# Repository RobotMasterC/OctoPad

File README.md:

## OctoPad

*Time is only for PCB*

An 8 key macro pad with 2 knobs that uses KMK firmware

*Image drawn by Ever*

*https://www.youtube.com/@Ever_Draws*

## BOM
- 8x DSA keycaps
- 8x Cherry MX Switches
- 8x SOM123 Diodes (or Any other 1N4148 Diode)
- 4x M3x16 Bolt
- 4x M3 Heatset
- 2x EC11 Rotary Encoder
- 1x XIAO RP2040

## Overall Image

## Schematic

## PCB

## Case

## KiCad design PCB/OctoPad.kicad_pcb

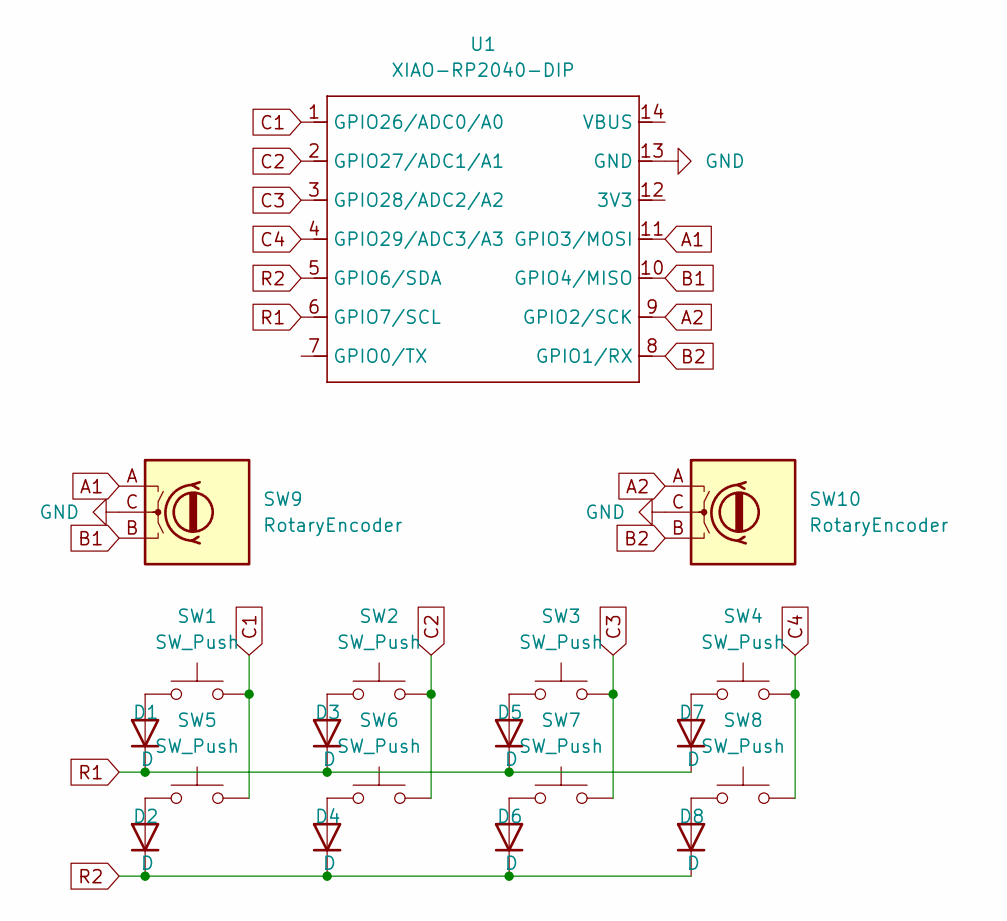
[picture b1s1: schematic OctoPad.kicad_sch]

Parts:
D1, D2, D3, D4, D5, D6, D7, D8: D; D_SOD123_axial
SW1, SW2, SW3, SW4, SW5, SW6, SW7, SW8: SW_Push; SW_Cherry_MX_1.00u_PCB
SW9, SW10: RotaryEncoder; RotaryEncoder_Alps_EC11E_Vertical_H20mm
U1: XIAO-RP2040-DIP

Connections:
A1: SW9.A, U1.11 (GPIO3/MOSI)
A2: SW10.A, U1.9 (GPIO2/SCK)
B1: SW9.B, U1.10 (GPIO4/MISO)
B2: SW10.B, U1.8 (GPIO1/RX)
C1: SW1.2, SW5.2, U1.1 (GPIO26/ADC0/A0)
C2: SW2.2, SW6.2, U1.2 (GPIO27/ADC1/A1)
C3: SW3.2, SW7.2, U1.3 (GPIO28/ADC2/A2)
C4: SW4.2, SW8.2, U1.4 (GPIO29/ADC3/A3)
GND: SW9.C, SW10.C, U1.13 (GND)
unnamed: D1.2 (A), SW1.1
unnamed: D2.2 (A), SW5.1
unnamed: D3.2 (A), SW2.1
unnamed: D4.2 (A), SW6.1
unnamed: D5.2 (A), SW3.1
unnamed: D6.2 (A), SW7.1
unnamed: D7.2 (A), SW4.1
unnamed: D8.2 (A), SW8.1
R1: D1.1 (K), D3.1 (K), D5.1 (K), D7.1 (K), U1.6 (GPIO7/SCL)
R2: D2.1 (K), D4.1 (K), D6.1 (K), D8.1 (K), U1.5 (GPIO6/SDA)

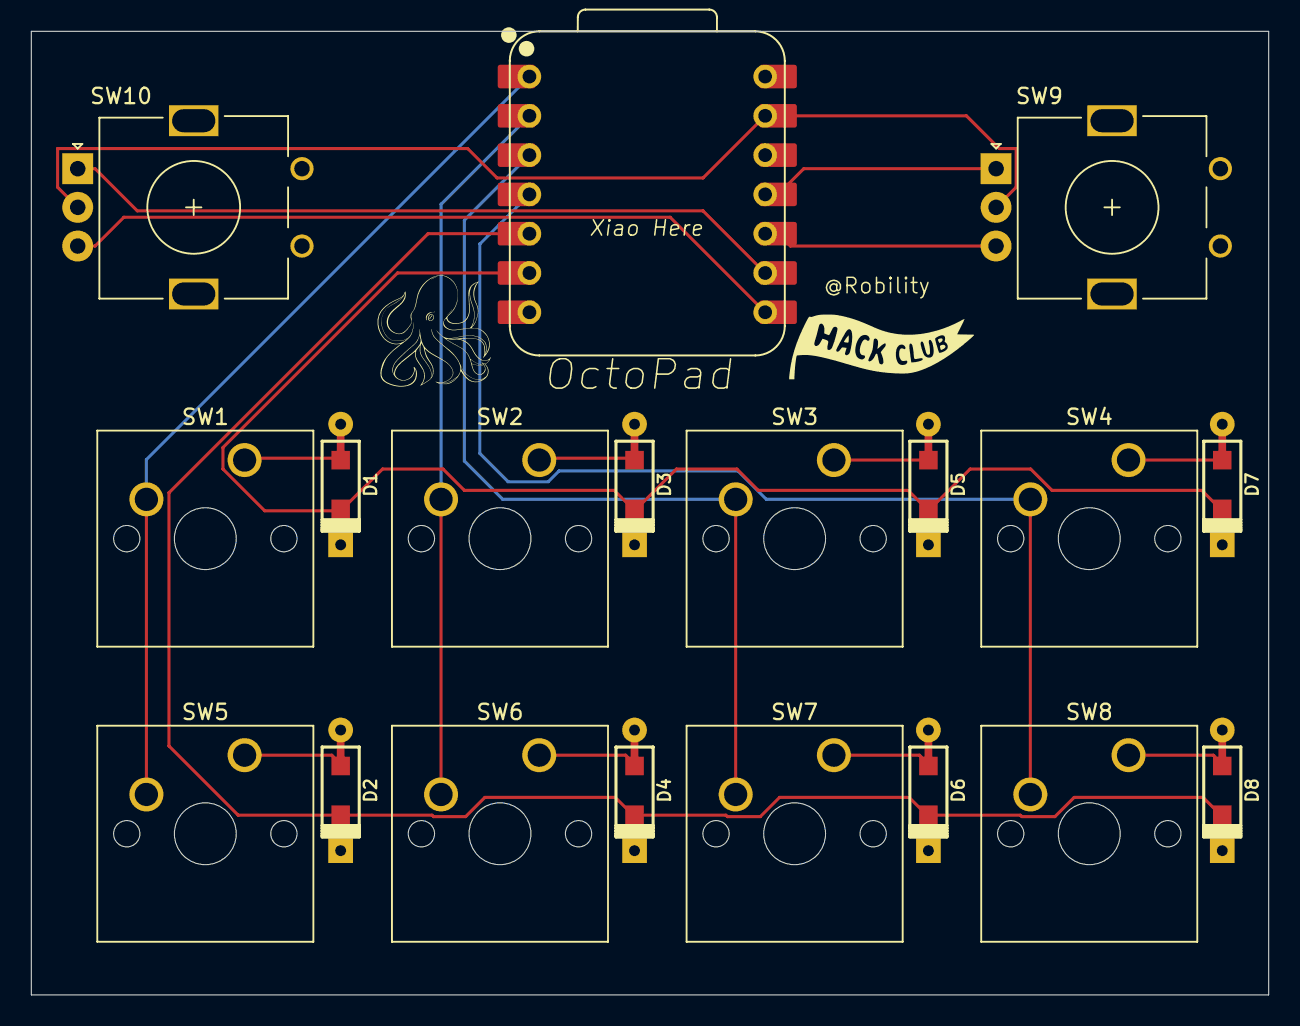
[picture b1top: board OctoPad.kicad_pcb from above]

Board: 2 copper layers, 80.0 x 62.3 mm, 19 parts (0 on the bottom side), 19 nets.

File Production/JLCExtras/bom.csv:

Designator,Footprint,Quantity,Value,LCSC Part #
"D1, D2, D3, D4, D5, D6, D7, D8",D_SOD123_axial,8,D,
"SW1, SW2, SW3, SW4, SW5, SW6, SW7, SW8",SW_Cherry_MX_1.00u_PCB,8,SW_Push,
"SW10, SW9",RotaryEncoder_Alps_EC11E_Vertical_H20mm,2,RotaryEncoder,
U1,XIAO-RP2040-DIP,1,XIAO-RP2040-DIP,
